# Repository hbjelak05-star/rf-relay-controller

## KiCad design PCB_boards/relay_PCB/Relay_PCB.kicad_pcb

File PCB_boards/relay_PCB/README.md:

This folder provides the schematic, PCB layout and 3D KiCad models of the Relay board.

This board has two purposes:
 
 -It receives signals via the male pin connector that turn ON/OFF the relay on the board.
 -It is connected to mains power (230V AC), convertes it 3.3V to power the receiver board through the male pin connectors.

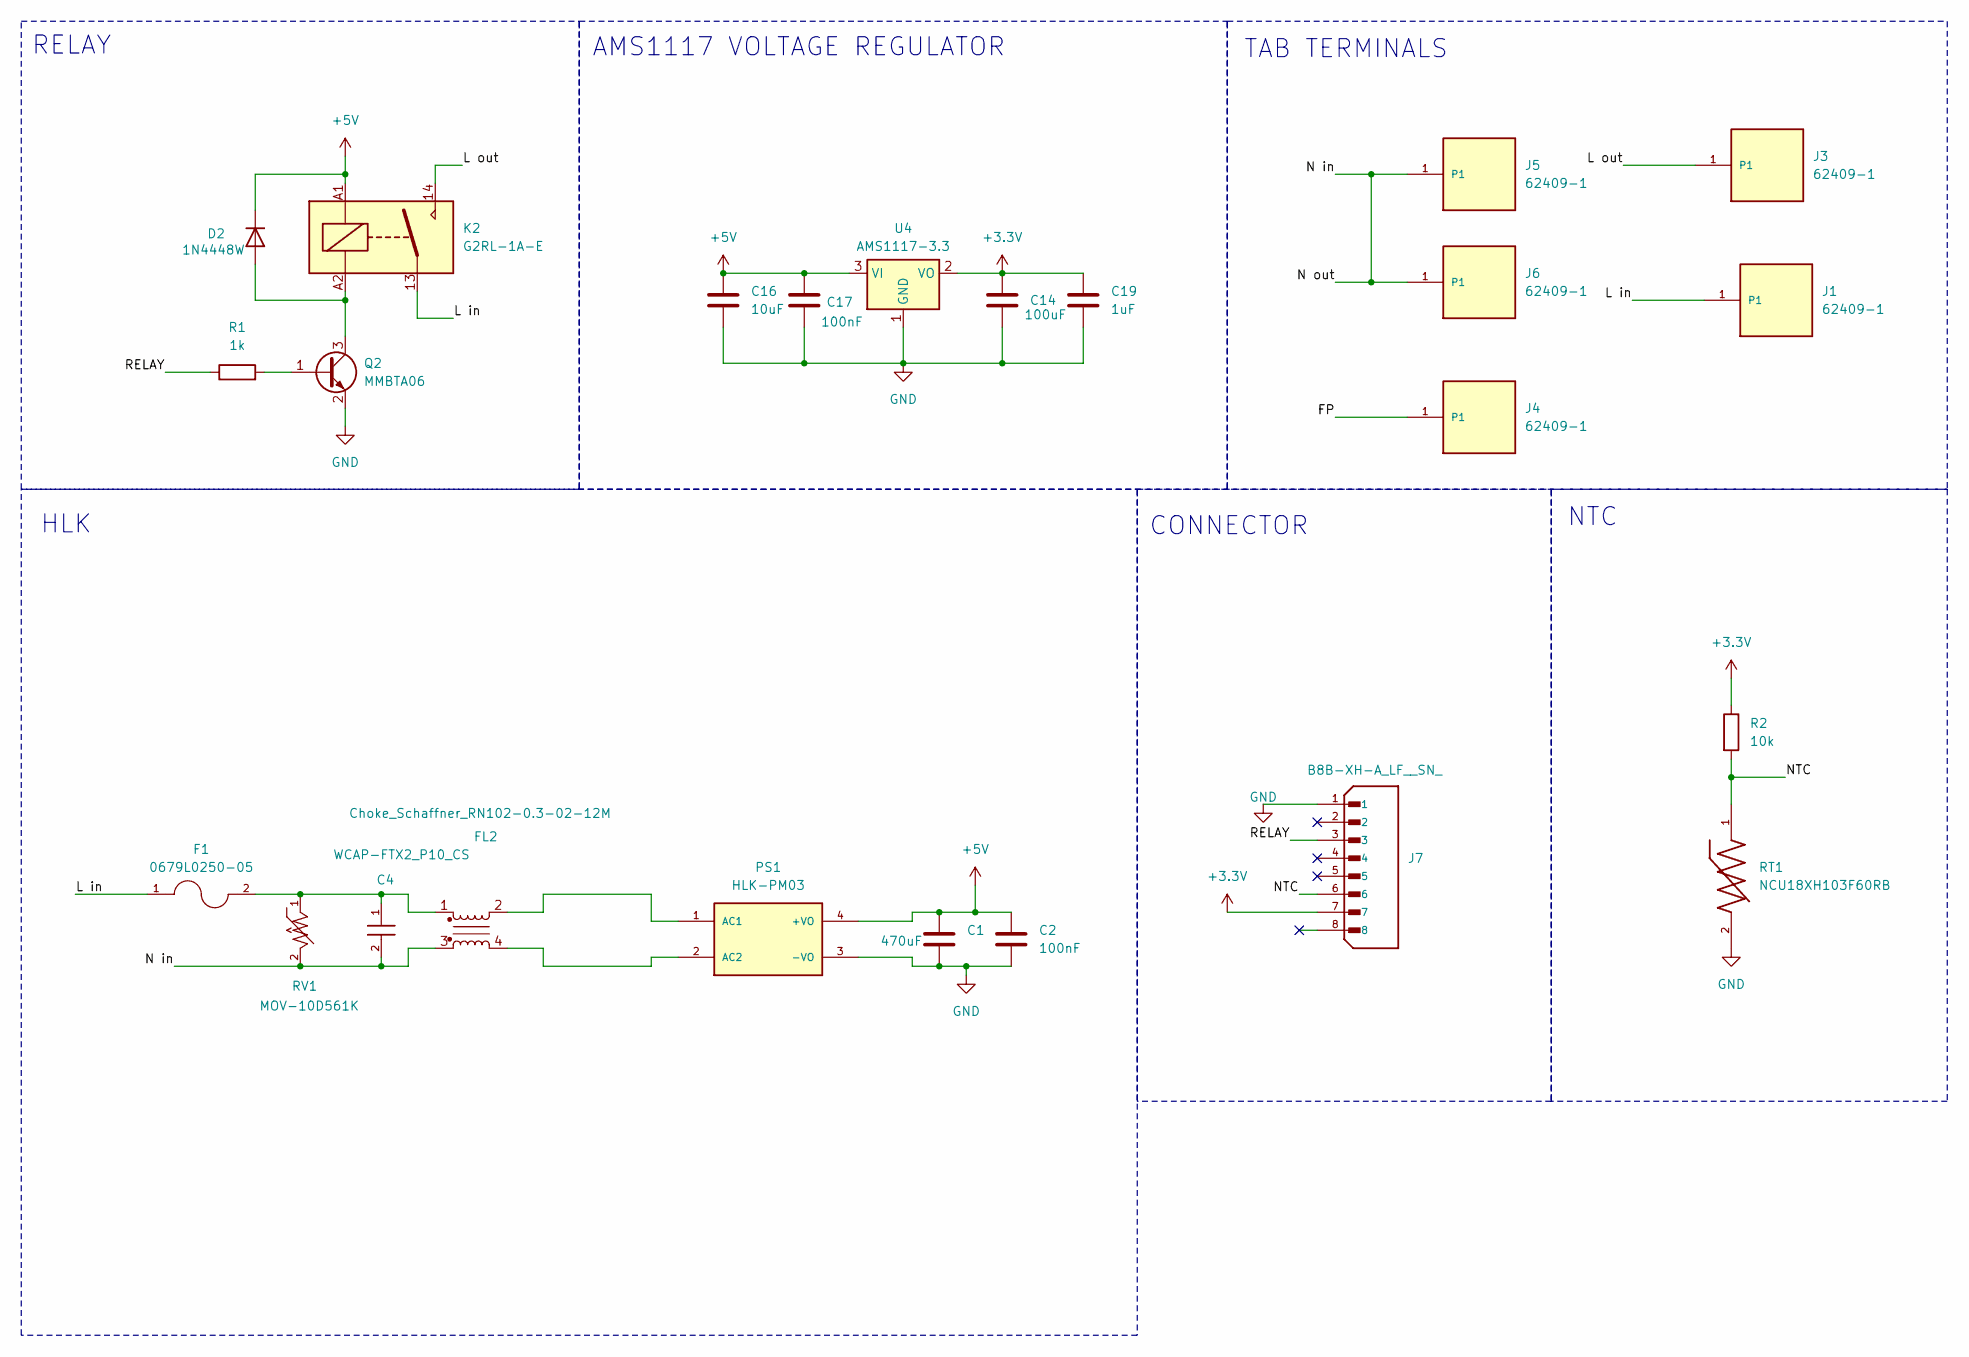
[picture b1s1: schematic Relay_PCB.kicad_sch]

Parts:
C1: 470uF; CP_Radial_D8.0mm_P3.50mm
C2, C17: 100nF; C_0603_1608Metric
C4: WCAP-FTX2_P10_CS; WCAP-FTX2_P10L13W7H13_CS
C14: 100uF; CP_Radial_D5.0mm_P2.00mm
C16: 10uF; C_1210_3225Metric
C19: 1uF; C_0603_1608Metric
D2: 1N4448W; D_SOD-123
F1: 0679L0250-05; FUSC6125X279N; PARTREV 0679H Apr2019
FL2: Choke_Schaffner_RN102-0.3-02-12M; Choke_Schaffner_RN102-04-14.0x14.0mm
J1, J3, J4, J5, J6: 62409-1; TE_62409-1; PART_DESCRIPTION CONN QC TAB 0.250 SOLDER
J7: B8B-XH-A_LF__SN_; JST_B8B-XH-A_LF__SN_; PARTREV 7/4/21
K2: G2RL-1A-E; Relay_SPST_Omron_G2RL-1A-E
PS1: HLK-PM03; CONV_HLK-PM03
Q2: MMBTA06; SOT-23
R1: 1k; R_0201_0603Metric
R2: 10k; R_0201_0603Metric
RT1: NCU18XH103F60RB; THRMC1608X95N
RV1: MOV-10D561K; VAR_MOV-10D561K; PARTREV 12/14/23R
U4: AMS1117-3.3; SOT-223-3_TabPin2

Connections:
+3.3V: C14.1, C19.1, J7.7, R2.1, U4.2 (VO)
+5V: C1.1, C2.1, C16.1, C17.1, D2.1 (K), K2.A1, PS1.4 (+VO), U4.3 (VI)
/FP: J4.1, J4.2 (P1)
/L in: F1.1, J1.1, J1.2 (P1), K2.13
/L out: J3.1, J3.2 (P1), K2.14
/N in: C4.2, FL2.3, J5.1, J5.2 (P1), J6.1, J6.2 (P1), RV1.2
/NTC: J7.6, R2.2, RT1.1
/RELAY: J7.3, R1.1
GND: C1.2, C2.2, C14.2, C16.2, C17.2, C19.2, J7.1, PS1.3 (-VO), Q2.2 (E), RT1.2, U4.1 (GND)
unnamed: C4.1, F1.2, FL2.1, RV1.1
unnamed: D2.2 (A), K2.A2, Q2.3 (C)
unnamed: FL2.2, PS1.1 (AC1)
unnamed: FL2.4, PS1.2 (AC2)
unnamed: Q2.1 (B), R1.2

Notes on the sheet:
CONNECTOR
AMS1117 VOLTAGE REGULATOR
HLK
TAB TERMINALS
NTC
RELAY

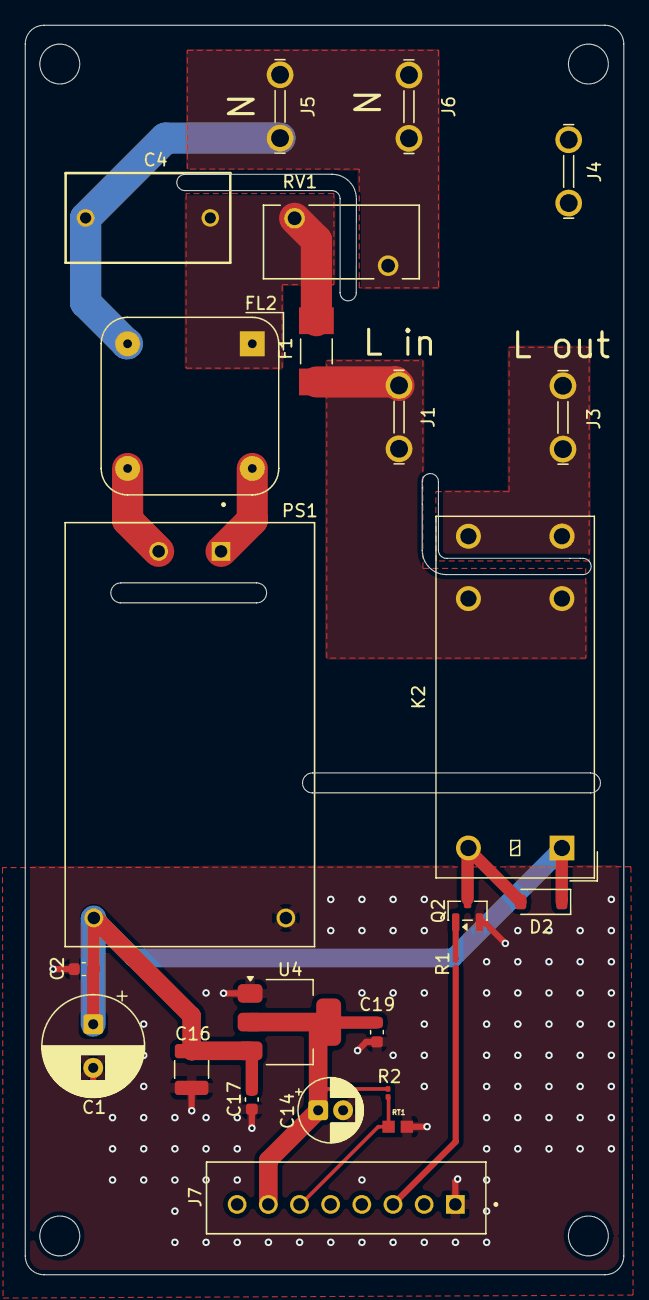
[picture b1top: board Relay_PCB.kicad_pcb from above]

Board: 2 copper layers, 48.0 x 100.2 mm, 24 parts (0 on the bottom side), 14 nets.

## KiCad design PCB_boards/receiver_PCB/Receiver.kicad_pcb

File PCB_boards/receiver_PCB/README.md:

This folder provides the schematic, PCB layout and 3D KiCad models of the receiver board.

The main purpose of this board it to receive RF signals form the transmitter board and forward those messages to the Relay board via the male pin connectors.

It receives a message form the transmitter board and depending on the message comand either turns the relay ON or OFF on the relay PCB board.

The Realy state is indicated by the LED on the board:
if the LED is Green = Relay ON
if the LED is Red = Relay OFF

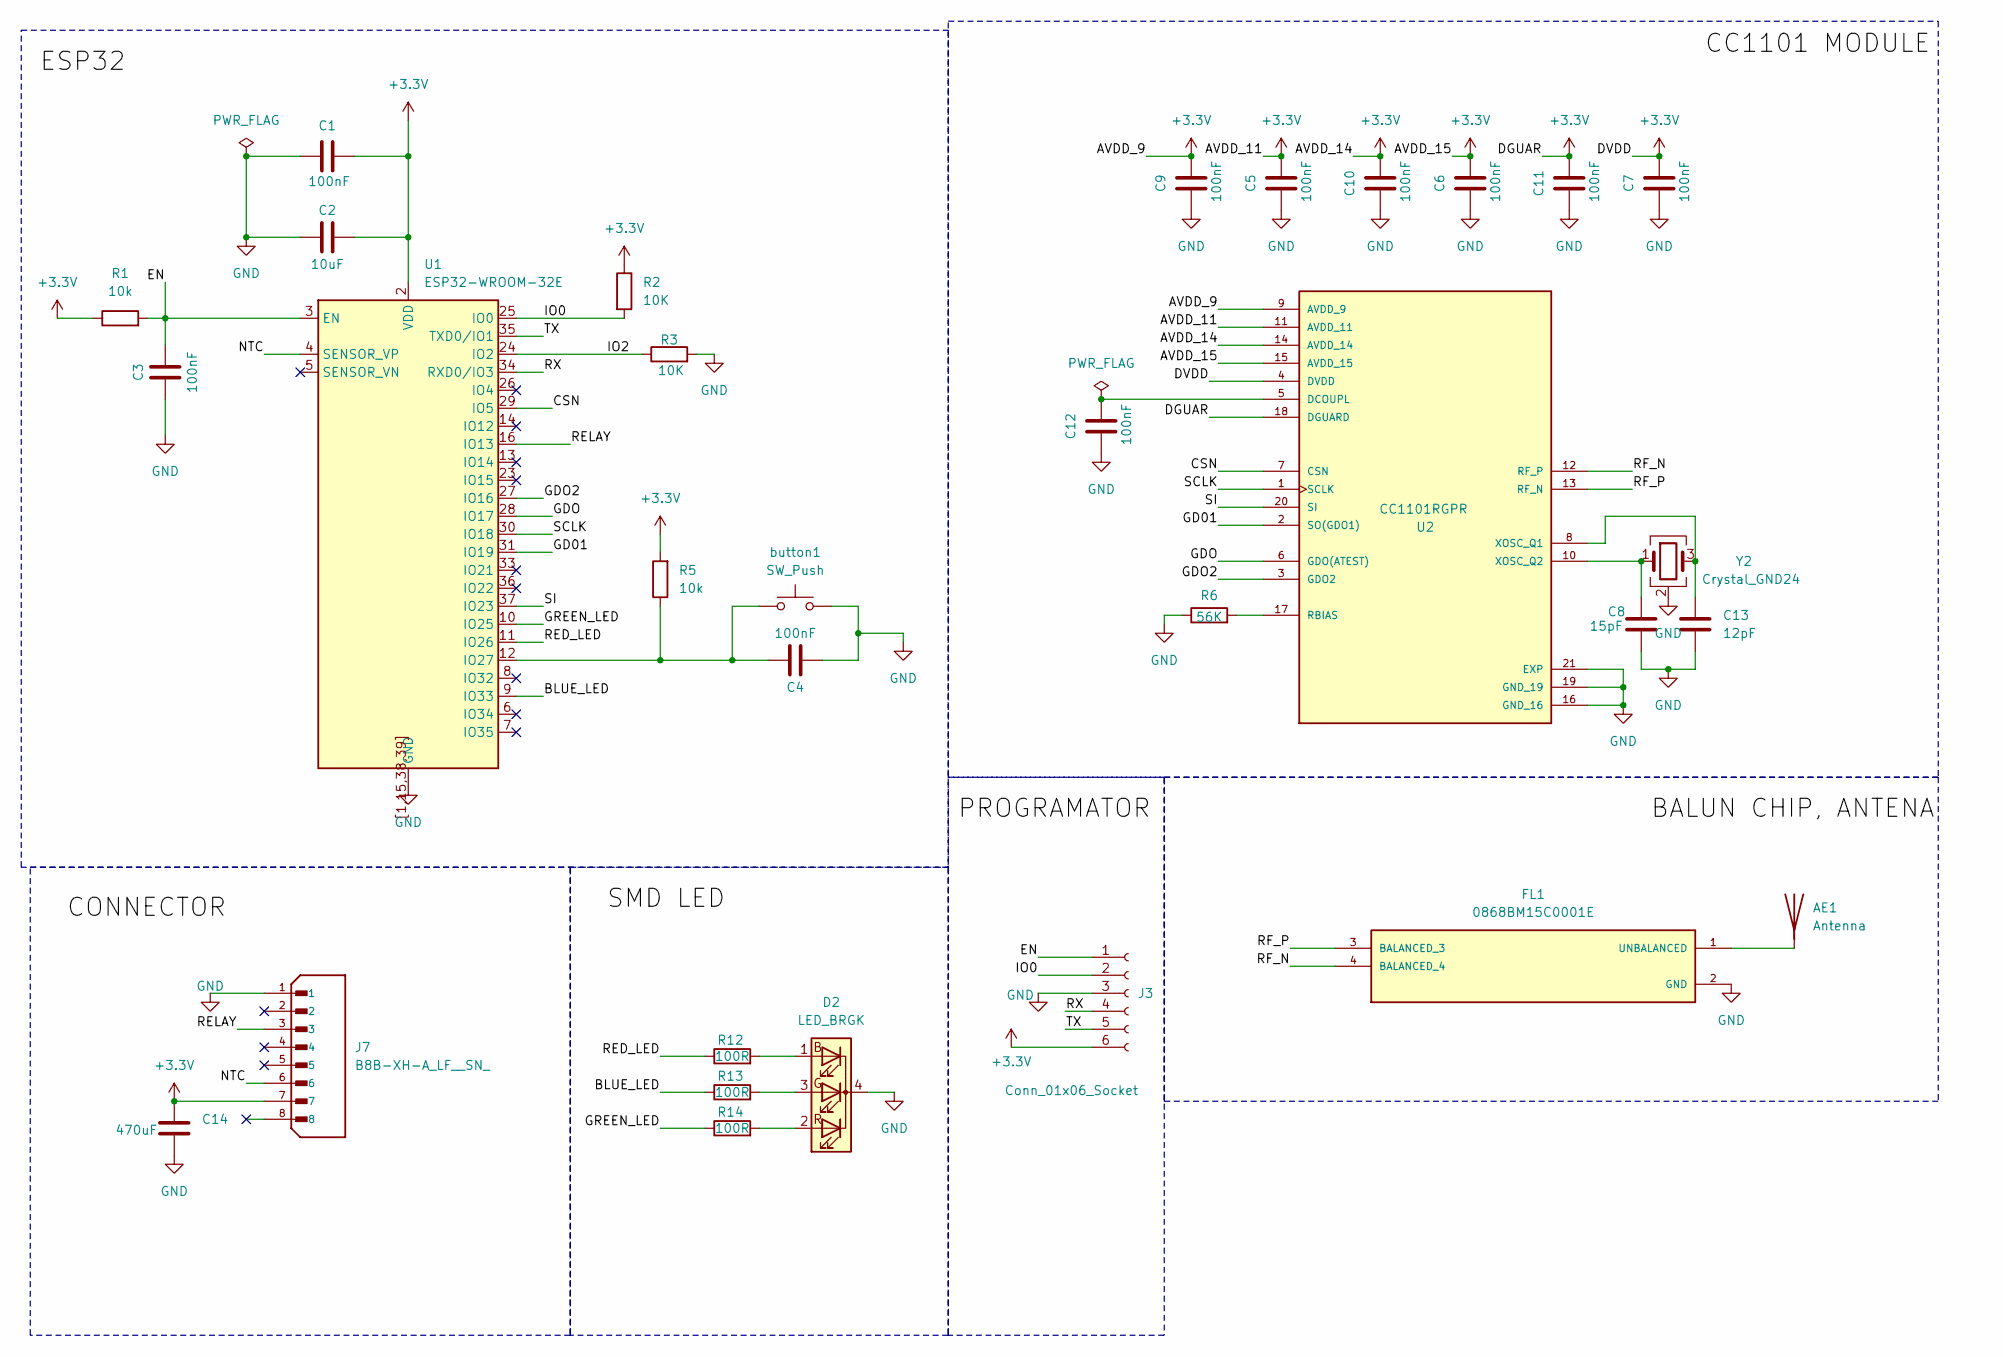
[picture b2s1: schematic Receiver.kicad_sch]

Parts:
AE1: Antenna; Texas_SWRA416_868MHz_915MHz
C1, C3, C4, C5, C6, C7, C9, C10, C11, C12: 100nF; C_0603_1608Metric
C2: 10uF; C_1210_3225Metric
C8: 15pF; C_0402_1005Metric
C13: 12pF; C_0402_1005Metric
C14: 470uF; CP_Radial_D8.0mm_P3.50mm
D2: LED_BRGK; LED_RGB_5050-6
FL1: 0868BM15C0001E; FIL_0868BM15C0001E; PARTREV 2.1
J3: Conn_01x06_Socket; PinHeader_1x06_P2.54mm_Vertical
J7: B8B-XH-A_LF__SN_; JST_B8B-XH-A_LF__SN_; PARTREV 7/4/21
R1, R5: 10k; R_0603_1608Metric
R2, R3: 10K; R_0603_1608Metric
R6: 56K; R_0402_1005Metric
R12, R13, R14: 100R; R_0603_1608Metric
U1: ESP32-WROOM-32E
U2: CC1101RGPR; QFN50P400X400X100-21N; PARTREV 6-May-2020
Y2: Crystal_GND24; Crystal_SMD_3225-4Pin_3.2x2.5mm
button1: SW_Push; SW_PUSH_6mm

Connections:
+3.3V: C1.2, C2.2, C5.2, C6.2, C7.2, C9.2, C10.2, C11.2, C14.1, J3.6, J7.7, R1.1, R2.1, R5.2, U1.2 (VDD), U2.4 (DVDD), U2.9 (AVDD_9), U2.11 (AVDD_11), U2.14 (AVDD_14), U2.15 (AVDD_15), U2.18 (DGUARD)
/BLUE_LED: R13.1, U1.9 (IO33)
/CSN: U1.29 (IO5), U2.7 (CSN)
/EN: C3.2, J3.1, R1.2, U1.3 (EN)
/GD01: U1.31 (IO19), U2.2 (SO(GDO1))
/GDO: U1.28 (IO17), U2.6 (GDO(ATEST))
/GDO2: U1.27 (IO16), U2.3 (GDO2)
/GREEN_LED: R14.1, U1.10 (IO25)
/IO0: J3.2, R2.2, U1.25 (IO0)
/IO2: R3.1, U1.24 (IO2)
/NTC: J7.6, U1.4 (SENSOR_VP)
/RED_LED: R12.1, U1.11 (IO26)
/RELAY: J7.3, U1.16 (IO13)
/RF_N: FL1.4 (BALANCED_4), U2.12 (RF_P)
/RF_P: FL1.3 (BALANCED_3), U2.13 (RF_N)
/RX: J3.4, U1.34 (RXD0/IO3)
/SCLK: U1.30 (IO18), U2.1 (SCLK)
/SI: U1.37 (IO23), U2.20 (SI)
/TX: J3.5, U1.35 (TXD0/IO1)
GND: C1.1, C2.1, C3.1, C4.1, C5.1, C6.1, C7.1, C8.2, C9.1, C10.1, C11.1, C12.1, C13.2, C14.2, D2.4 (K), FL1.2 (GND), FL1.5 (GND), FL1.6 (GND), J3.3, J7.1, R3.2, R6.1, U1.1 (GND), U1.15 (GND), U1.38 (GND), U1.39 (GND), U1.[1,15,38,39] (GND), U2.16 (GND_16), U2.19 (GND_19), U2.21 (EXP), Y2.2 (G), Y2.4 (G), button1.2
unnamed: AE1.1 (A_1), FL1.1 (UNBALANCED)
unnamed: D2.1 (BA), R12.2
unnamed: D2.3 (GA), R13.2
unnamed: D2.2 (RA), R14.2
unnamed: C4.2, R5.1, U1.12 (IO27), button1.1
unnamed: C12.2, U2.5 (DCOUPL)
unnamed: R6.2, U2.17 (RBIAS)
unnamed: C13.1, U2.8 (XOSC_Q1), Y2.3
unnamed: C8.1, U2.10 (XOSC_Q2), Y2.1

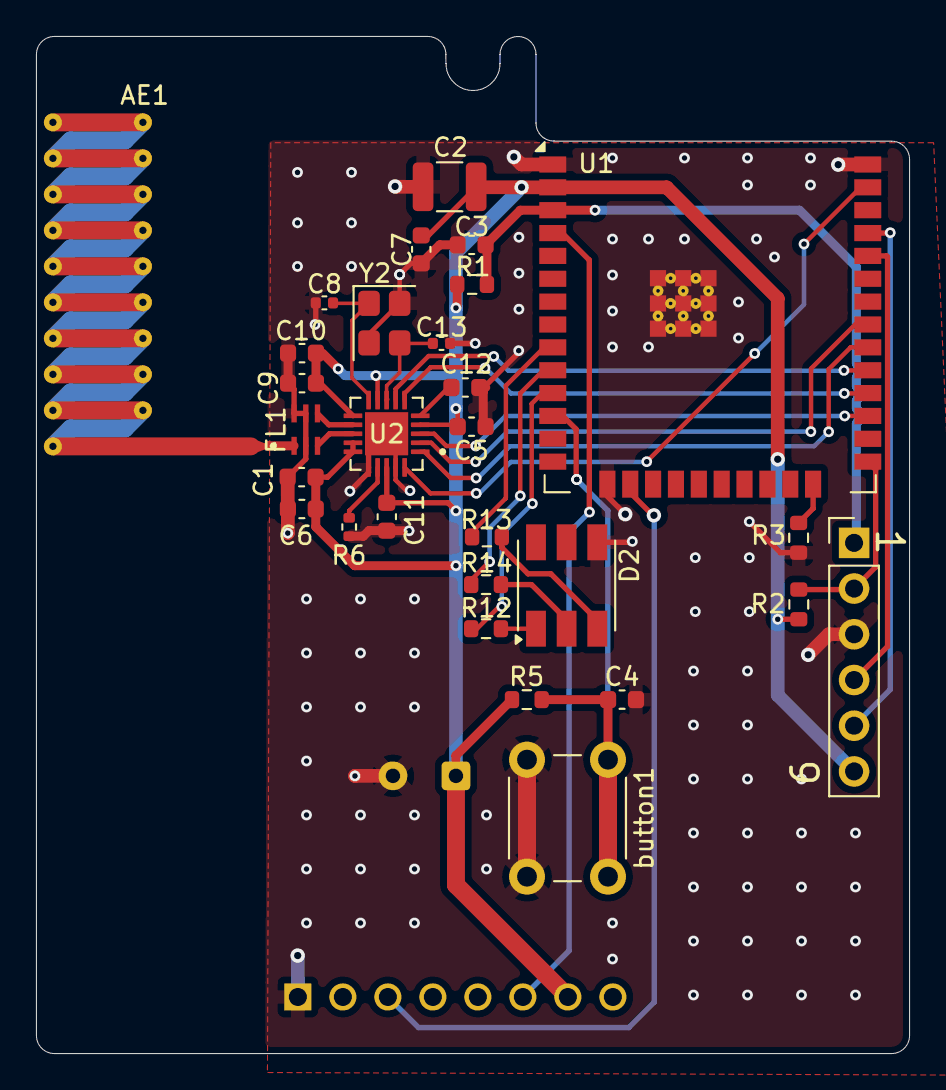
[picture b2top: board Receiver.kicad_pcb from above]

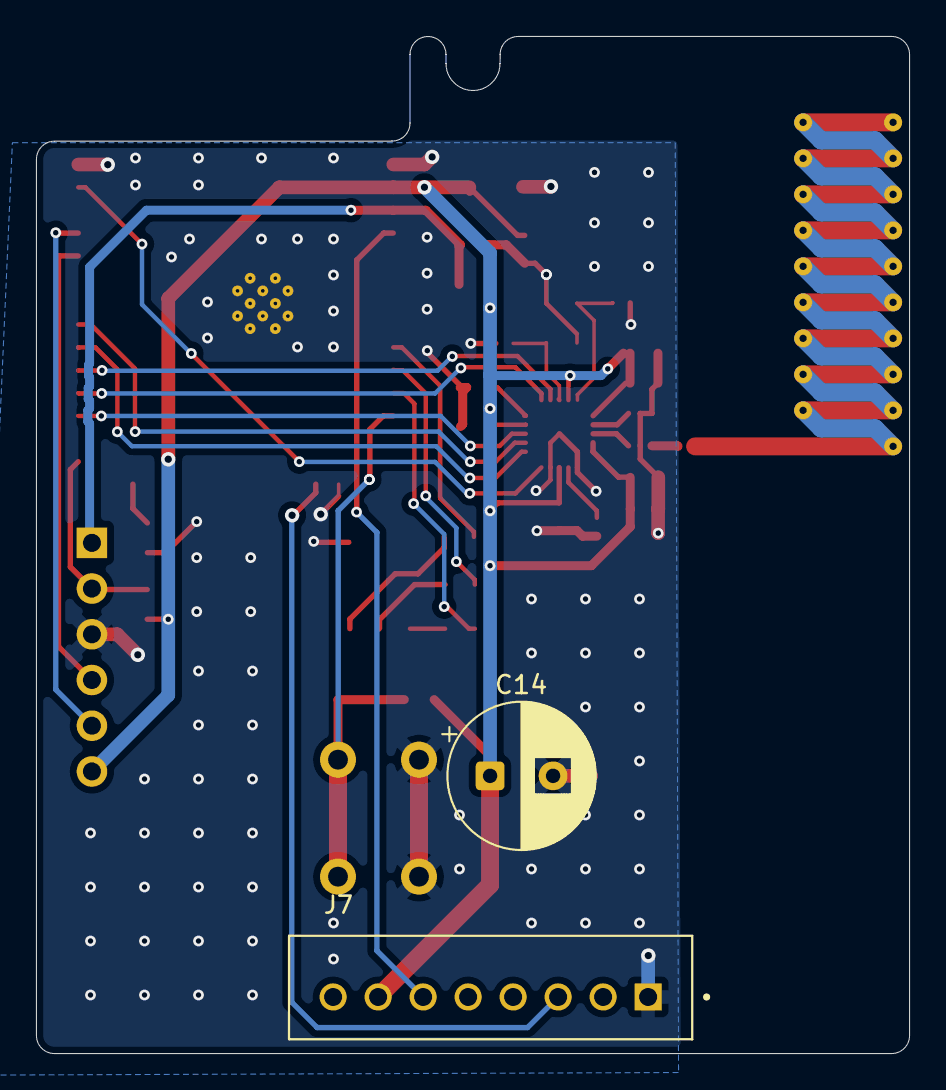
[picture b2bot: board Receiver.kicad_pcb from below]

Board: 2 copper layers, 48.5 x 56.5 mm, 31 parts (2 on the bottom side), 29 nets.
